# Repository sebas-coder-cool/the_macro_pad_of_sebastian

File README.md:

# zebra pad
## This is the zebra pad. with the zebra pad you kan replace your WASD keys were you game with.
images

[zebra pad.pdf](https://github.com/user-attachments/files/33282872/zebra.pad.pdf)

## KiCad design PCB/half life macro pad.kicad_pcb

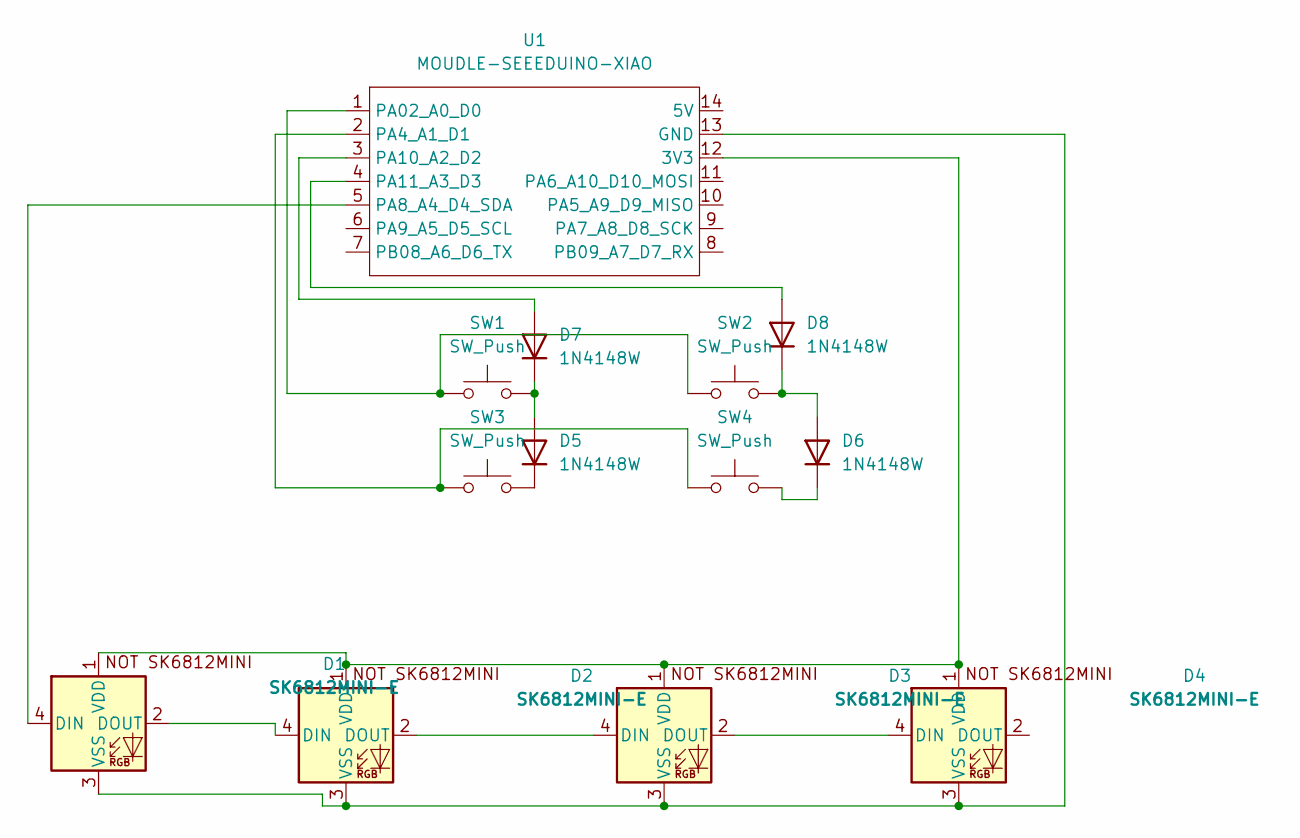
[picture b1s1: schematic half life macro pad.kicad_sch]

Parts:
D1, D2, D3, D4: SK6812MINI-E; LED_SK6812MINI_PLCC4_3.5x3.5mm_P1.75mm
D5, D6, D7, D8: 1N4148W; D_SOD-123
SW1, SW2, SW3, SW4: SW_Push; SW_Cherry_MX_1.00u_PCB
U1: MOUDLE-SEEEDUINO-XIAO; XIAO-Generic-Hybrid-14P-2.54-21X17.8MM

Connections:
unnamed: D1.4 (DIN), U1.5 (PA8_A4_D4_SDA)
unnamed: D1.2 (DOUT), D2.4 (DIN)
unnamed: D1.1 (VDD), D2.1 (VDD), D3.1 (VDD), D4.1 (VDD), U1.12 (3V3)
unnamed: D1.3 (VSS), D2.3 (VSS), D3.3 (VSS), D4.3 (VSS), U1.13 (GND)
unnamed: D2.2 (DOUT), D3.4 (DIN)
unnamed: D3.2 (DOUT), D4.4 (DIN)
unnamed: D5.2 (A), D7.1 (K), SW1.2
unnamed: D5.1 (K), SW3.2
unnamed: D6.2 (A), D8.1 (K), SW2.2
unnamed: D6.1 (K), SW4.2
unnamed: D7.2 (A), U1.3 (PA10_A2_D2)
unnamed: D8.2 (A), U1.4 (PA11_A3_D3)
unnamed: SW1.1, SW2.1, U1.1 (PA02_A0_D0)
unnamed: SW3.1, SW4.1, U1.2 (PA4_A1_D1)

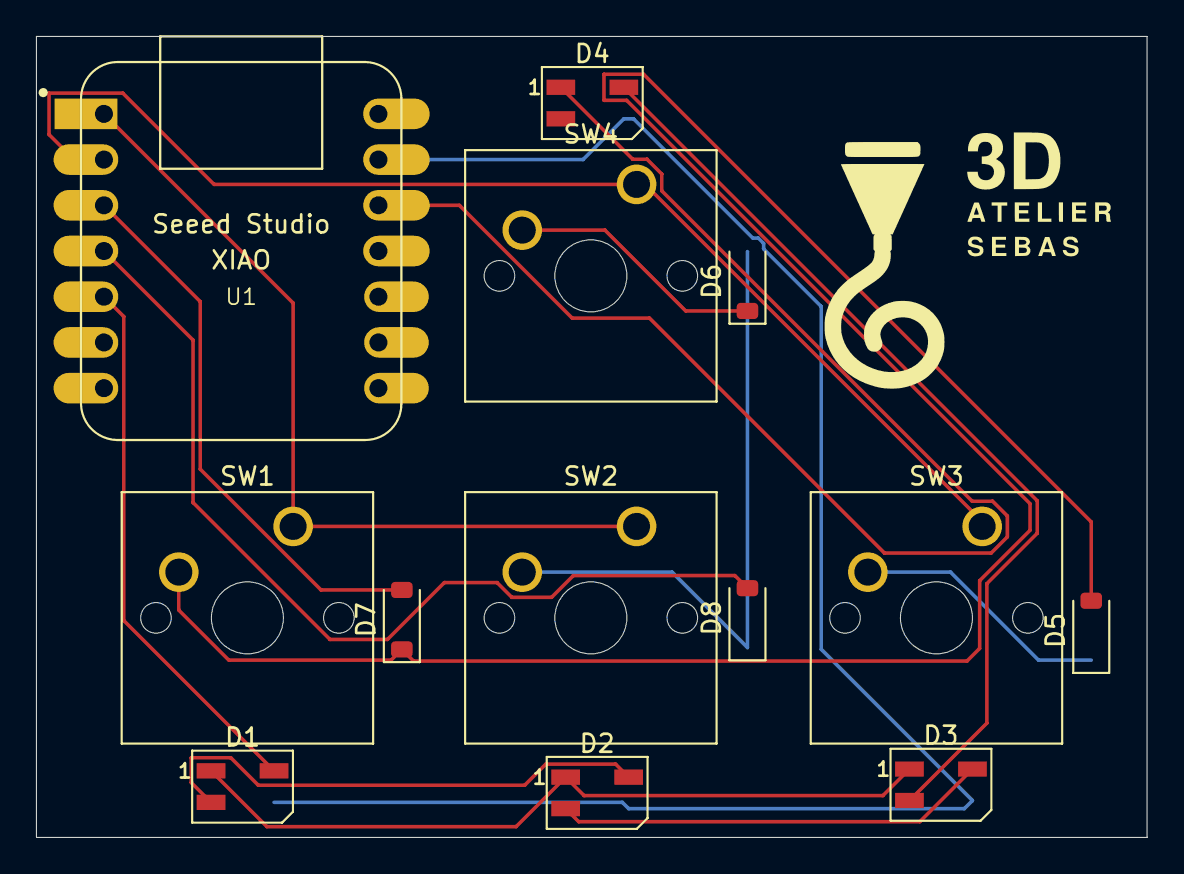
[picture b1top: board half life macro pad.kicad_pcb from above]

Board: 2 copper layers, 61.7 x 44.5 mm, 13 parts (0 on the bottom side), 14 nets.
